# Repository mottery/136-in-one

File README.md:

# 136-in-one
JIS配列日本語108キー＋マクロキー28キー一体型クソデカキーボード  
ほとんど自分用  
## kicad
回路図とPCB設計図が入っています  
|ファイル名|何これ|
| ---- | ---- |
|136inOne-layout.kicad_pcb|PCB設計図|
|136inOne-layout.kicad_pro|基板のプロジェクトファイル|
|136inOne-layout.kicad_sch|回路図|
|136inOne-layout_plate_frame.kicad_pcb|トッププレート（フレーム）の設計図|
|136inOne-layout_plate_frame.kicad_pro|トッププレートのプロジェクトファイル|
|136inOne-layout_plate_frame_bottom.kicad_pcb|ボトムプレートの設計図|
|136inOne-layout_plate_frame_bottom.kicad_pro|ボトムプレートのプロジェクトファイル|

## firmware
ビルド済みファームウェアやキーマッピングなど
|ファイル名|何これ|
| ---- | ---- |
|mottery_136_in_one_vial.uf2|ビルド済みファームウェア Vial対応|
|keyboard.json|キーボード定義ファイル|
|keymaps/vial/config.h|ヘッダファイル|
|keymaps/vial/keymap.c|キーマップファイル|
|keymaps/vial/rules.mk|Vial用設定ファイル|
|keymaps/vial/vial.json|Vial用定義ファイル|

## FAQ
Q：実用性は？  
A：少なくとも私にとっては実際実用な。

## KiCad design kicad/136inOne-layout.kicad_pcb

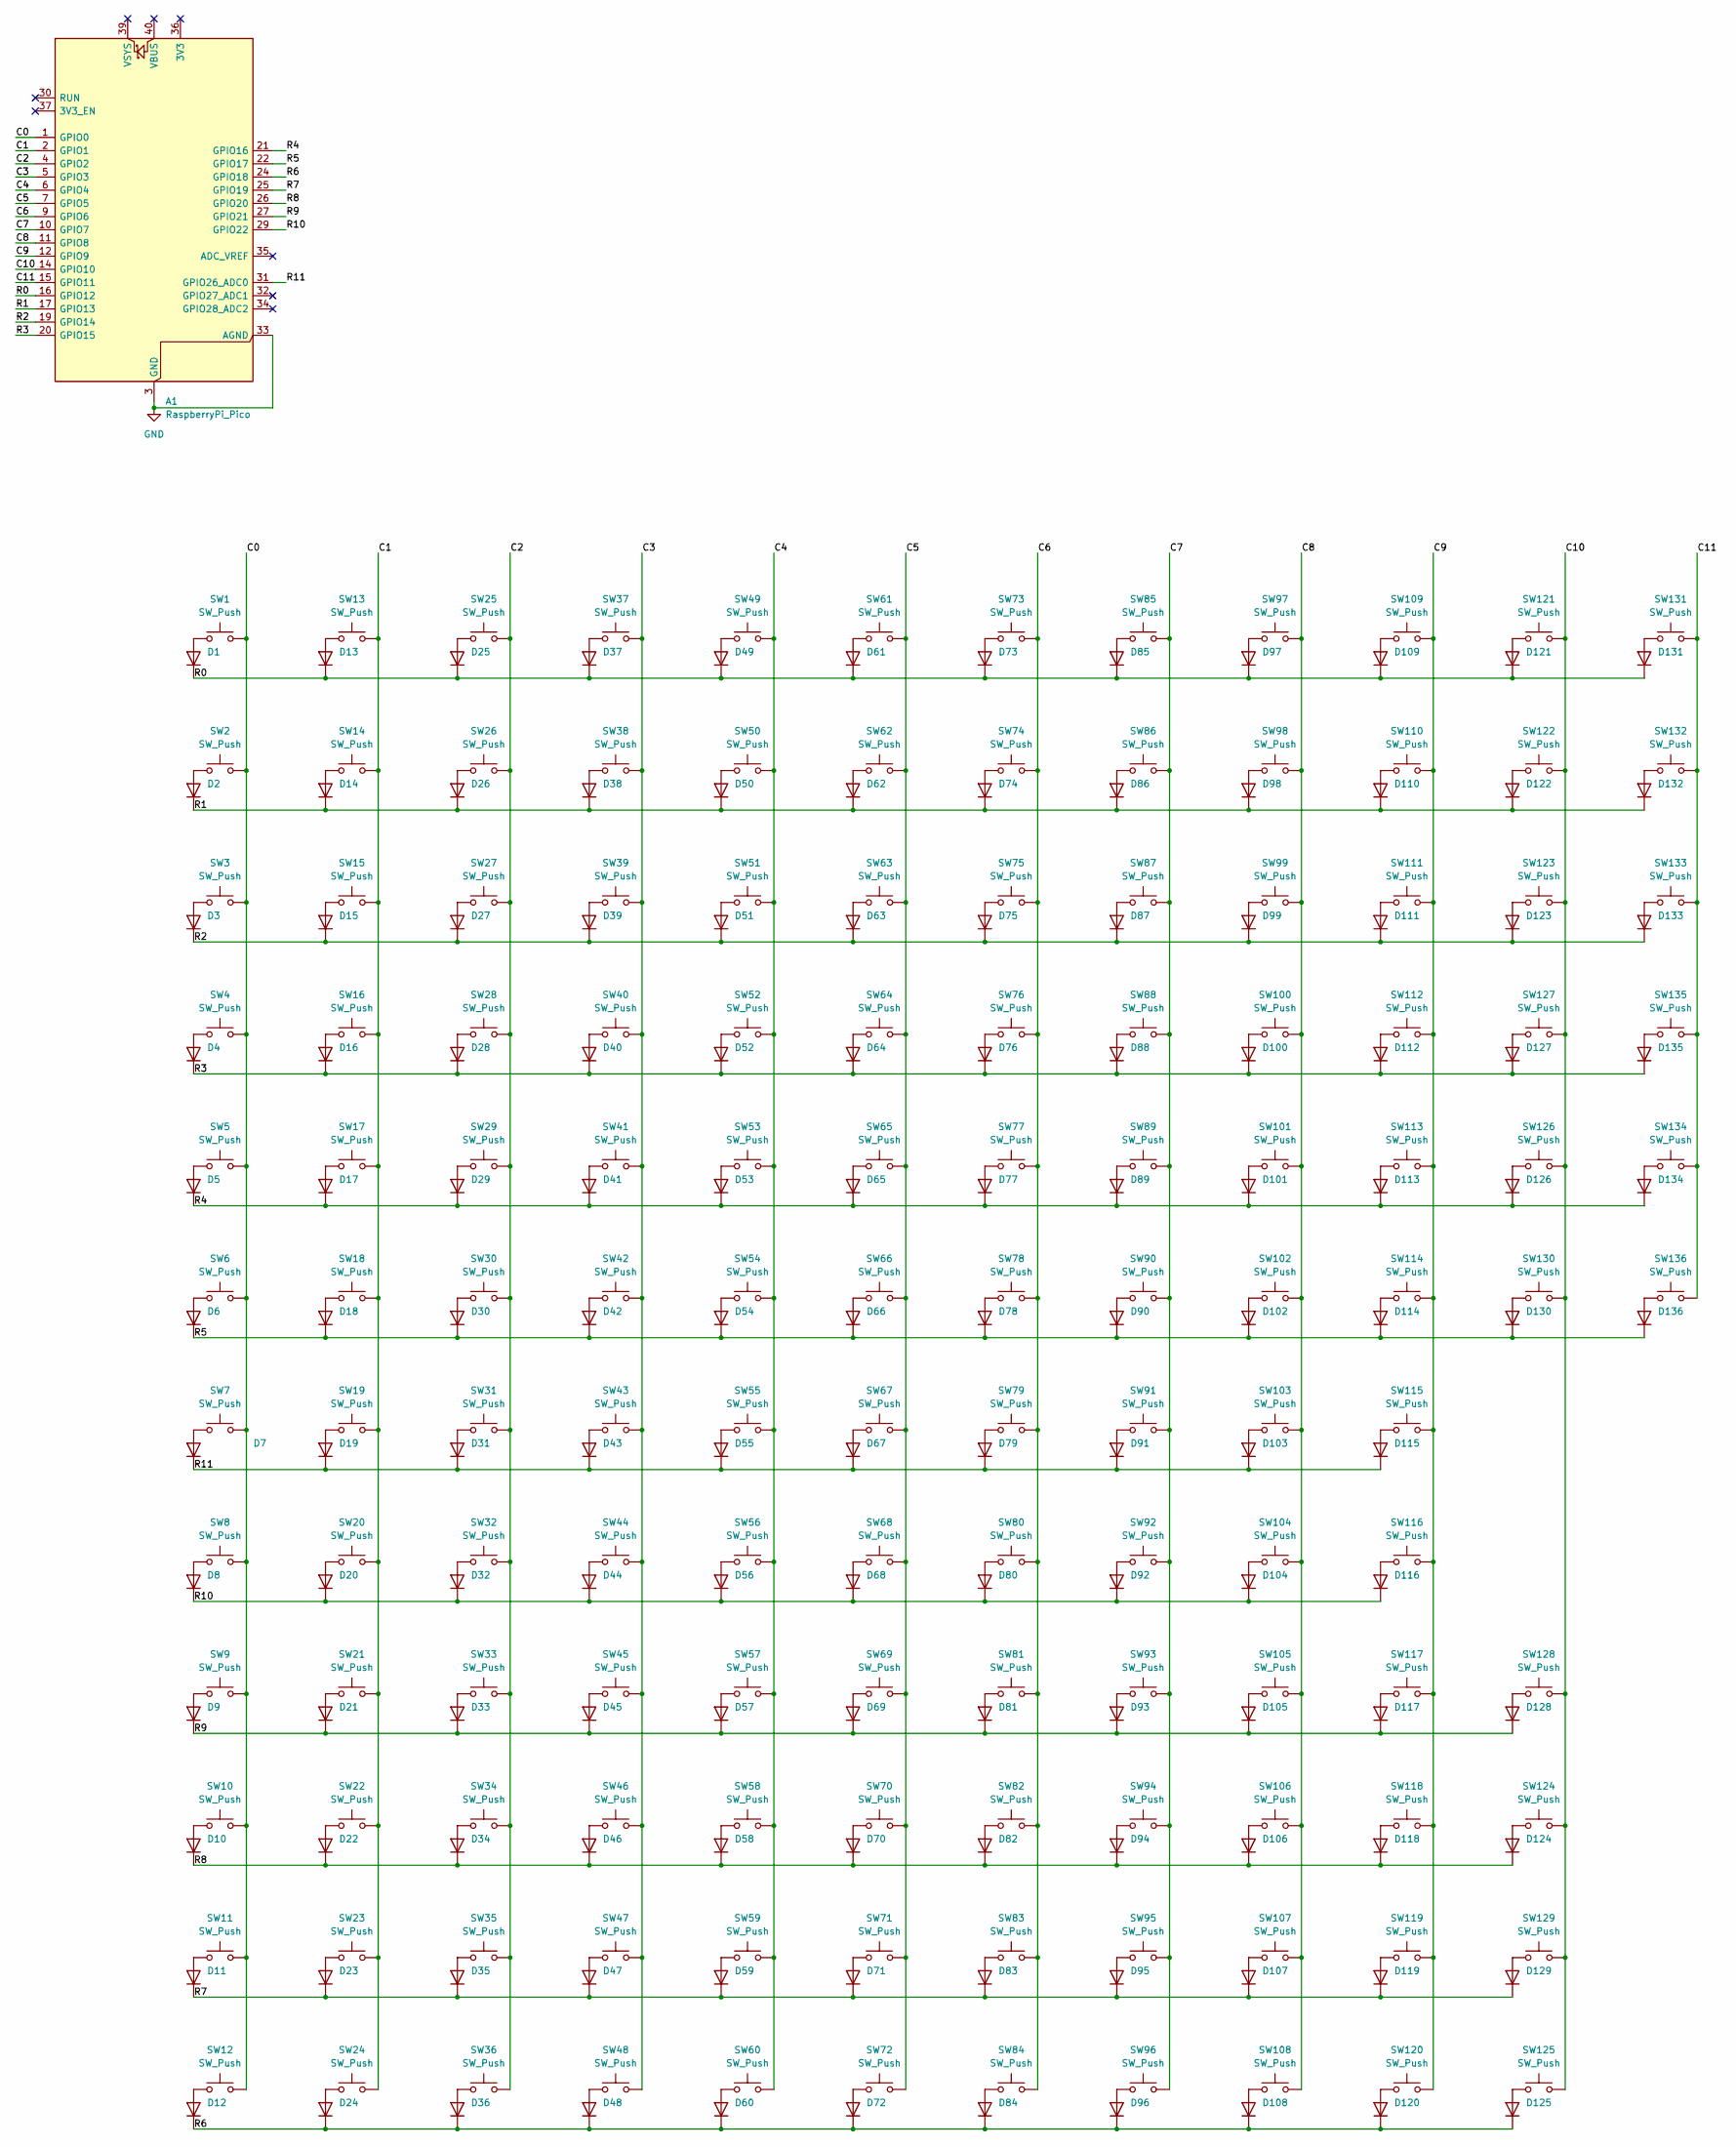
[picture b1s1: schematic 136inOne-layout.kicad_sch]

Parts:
A1: RaspberryPi_Pico; RaspberryPi_Pico_Common_THT
D1, D2, D3, D4, D5, D6, D7, D8, D9, D10, D11, D12, D13, D14, D15, D16, D17, D18, D19, D20, D21, D22, D23, D24, D25, D26, D27, D28, D29, D30, D31, D32, D33, D34, D35, D36, D37, D38, D39, D40, D41, D42, D43, D44, D45, D46, D47, D48, D49, D50, D51, D52, D53, D54, D55, D56, D57, D58, D59, D60, D61, D62, D63, D64, D65, D66, D67, D68, D69, D70, D71, D72, D73, D74, D75, D76, D77, D78, D79, D80, D81, D82, D83, D84, D85, D86, D87, D88, D89, D90, D91, D92, D93, D94, D95, D96, D97, D98, D99, D100, D101, D102, D103, D104, D105, D106, D107, D108, D109, D110, D111, D112, D113, D114, D115, D116, D117, D118, D119, D120, D121, D122, D123, D124, D125, D126, D127, D128, D129, D130, D131, D132, D133, D134, D135, D136: D; D_DO-35_SOD27_P7.62mm_Horizontal
SW1, SW2, SW3, SW4, SW5, SW6, SW7, SW8, SW9, SW10, SW11, SW12, SW13, SW14, SW15, SW16, SW17, SW18, SW19, SW20, SW21, SW22, SW23, SW24, SW25, SW26, SW27, SW28, SW29, SW30, SW31, SW32, SW33, SW34, SW35, SW36, SW37, SW38, SW39, SW40, SW41, SW42, SW43, SW44, SW45, SW46, SW47, SW48, SW49, SW50, SW51, SW52, SW53, SW54, SW56, SW57, SW58, SW59, SW60, SW61, SW62, SW63, SW64, SW65, SW66, SW67, SW69, SW70, SW71, SW72, SW73, SW74, SW76, SW77, SW78, SW79, SW81, SW82, SW83, SW84, SW85, SW86, SW87, SW88, SW89, SW90, SW91, SW92, SW93, SW94, SW95, SW96, SW97, SW98, SW99, SW101, SW102, SW103, SW104, SW105, SW106, SW107, SW108, SW109, SW110, SW111, SW113, SW114, SW115, SW116, SW118, SW119, SW120, SW121, SW123, SW125, SW130, SW132, SW133, SW134, SW136: SW_Push; SW_Cherry_MX_1.00u_PCB
SW55: SW_Push; SW_Cherry_MX_1.50u_PCB
SW68: SW_Push; SW_Cherry_MX_ISOEnter_PCB
SW75, SW117: SW_Push; SW_Cherry_MX_2.00u_Vertical_PCB
SW80, SW112: SW_Push; SW_Cherry_MX_1.75u_PCB
SW100: SW_Push; SW_Cherry_MX_2.25u_PCB
SW122, SW124, SW127, SW128, SW129, SW131: SW_Push; SW_Cherry_MX_1.25u_PCB
SW126: SW_Push; SW_Cherry_MX_4.5u_PCB_drawings
SW135: SW_Push; SW_Cherry_MX_2.00u_PCB

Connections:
/C0: A1.1 (GPIO0), SW1.2, SW2.2, SW3.2, SW4.2, SW5.2, SW6.2, SW7.2, SW8.2, SW9.2, SW10.2, SW11.2, SW12.2
/C1: A1.2 (GPIO1), SW13.2, SW14.2, SW15.2, SW16.2, SW17.2, SW18.2, SW19.2, SW20.2, SW21.2, SW22.2, SW23.2, SW24.2
/C2: A1.4 (GPIO2), SW25.2, SW26.2, SW27.2, SW28.2, SW29.2, SW30.2, SW31.2, SW32.2, SW33.2, SW34.2, SW35.2, SW36.2
/C3: A1.5 (GPIO3), SW37.2, SW38.2, SW39.2, SW40.2, SW41.2, SW42.2, SW43.2, SW44.2, SW45.2, SW46.2, SW47.2, SW48.2
/C4: A1.6 (GPIO4), SW49.2, SW50.2, SW51.2, SW52.2, SW53.2, SW54.2, SW55.2, SW56.2, SW57.2, SW58.2, SW59.2, SW60.2
/C5: A1.7 (GPIO5), SW61.2, SW62.2, SW63.2, SW64.2, SW65.2, SW66.2, SW67.2, SW68.2, SW69.2, SW70.2, SW71.2, SW72.2
/C6: A1.9 (GPIO6), SW73.2, SW74.2, SW75.2, SW76.2, SW77.2, SW78.2, SW79.2, SW80.2, SW81.2, SW82.2, SW83.2, SW84.2
/C7: A1.10 (GPIO7), SW85.2, SW86.2, SW87.2, SW88.2, SW89.2, SW90.2, SW91.2, SW92.2, SW93.2, SW94.2, SW95.2, SW96.2
/C8: A1.11 (GPIO8), SW97.2, SW98.2, SW99.2, SW100.2, SW101.2, SW102.2, SW103.2, SW104.2, SW105.2, SW106.2, SW107.2, SW108.2
/C9: A1.12 (GPIO9), SW109.2, SW110.2, SW111.2, SW112.2, SW113.2, SW114.2, SW115.2, SW116.2, SW117.2, SW118.2, SW119.2, SW120.2
/C10: A1.14 (GPIO10), SW121.2, SW122.2, SW123.2, SW124.2, SW125.2, SW126.2, SW127.2, SW128.2, SW129.2, SW130.2
/C11: A1.15 (GPIO11), SW131.2, SW132.2, SW133.2, SW134.2, SW135.2, SW136.2
/R0: A1.16 (GPIO12), D1.1 (K), D13.1 (K), D25.1 (K), D37.1 (K), D49.1 (K), D61.1 (K), D73.1 (K), D85.1 (K), D97.1 (K), D109.1 (K), D121.1 (K), D131.1 (K)
/R1: A1.17 (GPIO13), D2.1 (K), D14.1 (K), D26.1 (K), D38.1 (K), D50.1 (K), D62.1 (K), D74.1 (K), D86.1 (K), D98.1 (K), D110.1 (K), D122.1 (K), D132.1 (K)
/R2: A1.19 (GPIO14), D3.1 (K), D15.1 (K), D27.1 (K), D39.1 (K), D51.1 (K), D63.1 (K), D75.1 (K), D87.1 (K), D99.1 (K), D111.1 (K), D123.1 (K), D133.1 (K)
/R3: A1.20 (GPIO15), D4.1 (K), D16.1 (K), D28.1 (K), D40.1 (K), D52.1 (K), D64.1 (K), D76.1 (K), D88.1 (K), D100.1 (K), D112.1 (K), D127.1 (K), D135.1 (K)
/R4: A1.21 (GPIO16), D5.1 (K), D17.1 (K), D29.1 (K), D41.1 (K), D53.1 (K), D65.1 (K), D77.1 (K), D89.1 (K), D101.1 (K), D113.1 (K), D126.1 (K), D134.1 (K)
/R5: A1.22 (GPIO17), D6.1 (K), D18.1 (K), D30.1 (K), D42.1 (K), D54.1 (K), D66.1 (K), D78.1 (K), D90.1 (K), D102.1 (K), D114.1 (K), D130.1 (K), D136.1 (K)
/R6: A1.24 (GPIO18), D12.1 (K), D24.1 (K), D36.1 (K), D48.1 (K), D60.1 (K), D72.1 (K), D84.1 (K), D96.1 (K), D108.1 (K), D120.1 (K), D125.1 (K)
/R7: A1.25 (GPIO19), D11.1 (K), D23.1 (K), D35.1 (K), D47.1 (K), D59.1 (K), D71.1 (K), D83.1 (K), D95.1 (K), D107.1 (K), D119.1 (K), D129.1 (K)
/R8: A1.26 (GPIO20), D10.1 (K), D22.1 (K), D34.1 (K), D46.1 (K), D58.1 (K), D70.1 (K), D82.1 (K), D94.1 (K), D106.1 (K), D118.1 (K), D124.1 (K)
/R9: A1.27 (GPIO21), D9.1 (K), D21.1 (K), D33.1 (K), D45.1 (K), D57.1 (K), D69.1 (K), D81.1 (K), D93.1 (K), D105.1 (K), D117.1 (K), D128.1 (K)
/R10: A1.29 (GPIO22), D8.1 (K), D20.1 (K), D32.1 (K), D44.1 (K), D56.1 (K), D68.1 (K), D80.1 (K), D92.1 (K), D104.1 (K), D116.1 (K)
/R11: A1.31 (GPIO26_ADC0), D7.1 (K), D19.1 (K), D31.1 (K), D43.1 (K), D55.1 (K), D67.1 (K), D79.1 (K), D91.1 (K), D103.1 (K), D115.1 (K)
GND: A1.3 (GND), A1.8 (GND), A1.13 (GND), A1.18 (GND), A1.23 (GND), A1.28 (GND), A1.33 (AGND), A1.38 (GND)
unnamed: D1.2 (A), SW1.1
unnamed: D2.2 (A), SW2.1
unnamed: D3.2 (A), SW3.1
unnamed: D4.2 (A), SW4.1
unnamed: D5.2 (A), SW5.1
unnamed: D6.2 (A), SW6.1
unnamed: D7.2 (A), SW7.1
unnamed: D8.2 (A), SW8.1
unnamed: D9.2 (A), SW9.1
unnamed: D10.2 (A), SW10.1
unnamed: D11.2 (A), SW11.1
unnamed: D12.2 (A), SW12.1
unnamed: D13.2 (A), SW13.1
unnamed: D14.2 (A), SW14.1
unnamed: D15.2 (A), SW15.1
unnamed: D16.2 (A), SW16.1
unnamed: D17.2 (A), SW17.1
unnamed: D18.2 (A), SW18.1
unnamed: D19.2 (A), SW19.1
unnamed: D20.2 (A), SW20.1
unnamed: D21.2 (A), SW21.1
unnamed: D22.2 (A), SW22.1
unnamed: D23.2 (A), SW23.1
unnamed: D24.2 (A), SW24.1
unnamed: D25.2 (A), SW25.1
unnamed: D26.2 (A), SW26.1
unnamed: D27.2 (A), SW27.1
unnamed: D28.2 (A), SW28.1
unnamed: D29.2 (A), SW29.1
unnamed: D30.2 (A), SW30.1
unnamed: D31.2 (A), SW31.1
unnamed: D32.2 (A), SW32.1
unnamed: D33.2 (A), SW33.1
unnamed: D34.2 (A), SW34.1
unnamed: D35.2 (A), SW35.1
unnamed: D36.2 (A), SW36.1
unnamed: D37.2 (A), SW37.1
unnamed: D38.2 (A), SW38.1
unnamed: D39.2 (A), SW39.1
unnamed: D40.2 (A), SW40.1
unnamed: D41.2 (A), SW41.1
unnamed: D42.2 (A), SW42.1
unnamed: D43.2 (A), SW43.1
unnamed: D44.2 (A), SW44.1
unnamed: D45.2 (A), SW45.1
unnamed: D46.2 (A), SW46.1
unnamed: D47.2 (A), SW47.1
unnamed: D48.2 (A), SW48.1
unnamed: D49.2 (A), SW49.1
unnamed: D50.2 (A), SW50.1
unnamed: D51.2 (A), SW51.1
unnamed: D52.2 (A), SW52.1
unnamed: D53.2 (A), SW53.1
unnamed: D54.2 (A), SW54.1
unnamed: D55.2 (A), SW55.1
unnamed: D56.2 (A), SW56.1
unnamed: D57.2 (A), SW57.1
unnamed: D58.2 (A), SW58.1
unnamed: D59.2 (A), SW59.1
unnamed: D60.2 (A), SW60.1
unnamed: D61.2 (A), SW61.1
unnamed: D62.2 (A), SW62.1
unnamed: D63.2 (A), SW63.1
unnamed: D64.2 (A), SW64.1
unnamed: D65.2 (A), SW65.1
unnamed: D66.2 (A), SW66.1
unnamed: D67.2 (A), SW67.1
unnamed: D68.2 (A), SW68.1
unnamed: D69.2 (A), SW69.1
unnamed: D70.2 (A), SW70.1
unnamed: D71.2 (A), SW71.1
unnamed: D72.2 (A), SW72.1
unnamed: D73.2 (A), SW73.1
unnamed: D74.2 (A), SW74.1
unnamed: D75.2 (A), SW75.1
unnamed: D76.2 (A), SW76.1
unnamed: D77.2 (A), SW77.1
unnamed: D78.2 (A), SW78.1
unnamed: D79.2 (A), SW79.1
unnamed: D80.2 (A), SW80.1
unnamed: D81.2 (A), SW81.1
unnamed: D82.2 (A), SW82.1
unnamed: D83.2 (A), SW83.1
unnamed: D84.2 (A), SW84.1
unnamed: D85.2 (A), SW85.1
unnamed: D86.2 (A), SW86.1
unnamed: D87.2 (A), SW87.1
unnamed: D88.2 (A), SW88.1
unnamed: D89.2 (A), SW89.1
unnamed: D90.2 (A), SW90.1
unnamed: D91.2 (A), SW91.1
unnamed: D92.2 (A), SW92.1
unnamed: D93.2 (A), SW93.1
unnamed: D94.2 (A), SW94.1
unnamed: D95.2 (A), SW95.1
unnamed: D96.2 (A), SW96.1
unnamed: D97.2 (A), SW97.1
unnamed: D98.2 (A), SW98.1
unnamed: D99.2 (A), SW99.1
unnamed: D100.2 (A), SW100.1
unnamed: D101.2 (A), SW101.1
unnamed: D102.2 (A), SW102.1
unnamed: D103.2 (A), SW103.1
unnamed: D104.2 (A), SW104.1
unnamed: D105.2 (A), SW105.1
unnamed: D106.2 (A), SW106.1
unnamed: D107.2 (A), SW107.1
unnamed: D108.2 (A), SW108.1
unnamed: D109.2 (A), SW109.1
unnamed: D110.2 (A), SW110.1
unnamed: D111.2 (A), SW111.1
unnamed: D112.2 (A), SW112.1
unnamed: D113.2 (A), SW113.1
unnamed: D114.2 (A), SW114.1
unnamed: D115.2 (A), SW115.1
unnamed: D116.2 (A), SW116.1
unnamed: D117.2 (A), SW117.1
unnamed: D118.2 (A), SW118.1
unnamed: D119.2 (A), SW119.1
unnamed: D120.2 (A), SW120.1
unnamed: D121.2 (A), SW121.1
unnamed: D122.2 (A), SW122.1
unnamed: D123.2 (A), SW123.1
unnamed: D124.2 (A), SW124.1
unnamed: D125.2 (A), SW125.1
unnamed: D126.2 (A), SW126.1
unnamed: D127.2 (A), SW127.1
unnamed: D128.2 (A), SW128.1
unnamed: D129.2 (A), SW129.1
unnamed: D130.2 (A), SW130.1
unnamed: D131.2 (A), SW131.1
unnamed: D132.2 (A), SW132.1
unnamed: D133.2 (A), SW133.1
unnamed: D134.2 (A), SW134.1
unnamed: D135.2 (A), SW135.1
unnamed: D136.2 (A), SW136.1

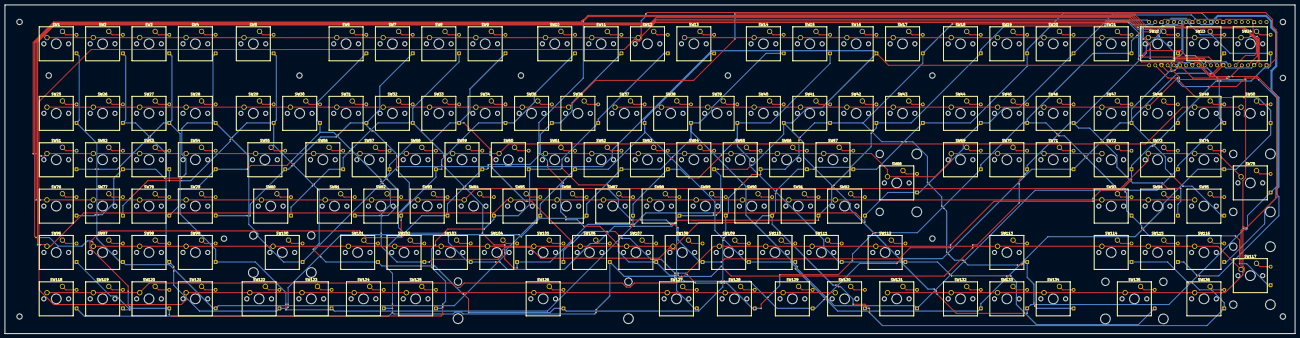
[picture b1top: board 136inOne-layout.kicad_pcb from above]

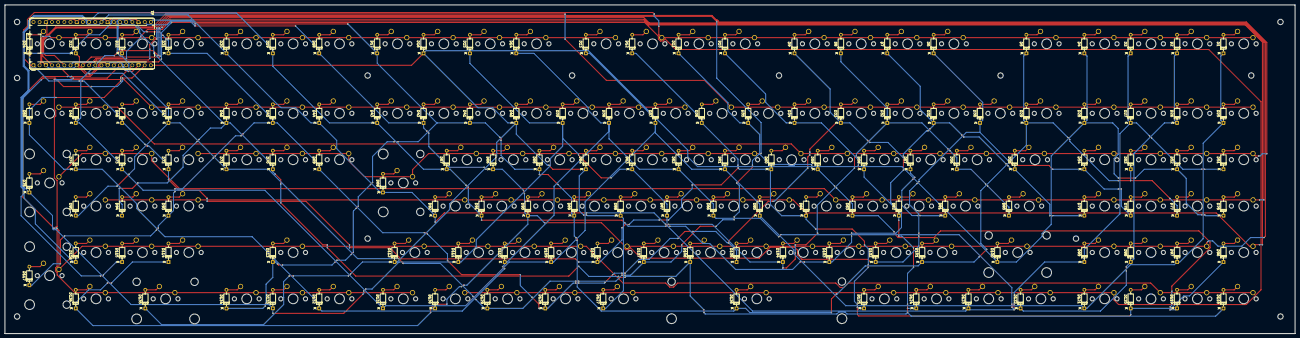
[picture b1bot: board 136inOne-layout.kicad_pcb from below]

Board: 2 copper layers, 530.0 x 135.0 mm, 273 parts (137 on the bottom side), 161 nets.
